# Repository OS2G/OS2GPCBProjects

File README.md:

# OS2GPCBProjects
Repo for the PCB projects

## Resources:

- [Keyboard Project Example](https://www.masterzen.fr/2020/05/03/designing-a-keyboard-part-1/)
- [Part Schematics](https://app.ultralibrarian.com/details/718f6c74-6ffb-11eb-9033-0a34d6323d74/Raspberry-Pi/RP2040)
- [Dr Bauer Kicard Intro Videos](https://youtube.com/@markatlnk5982?feature=shared)
- [RP2040 Spec Sheet](https://datasheets.raspberrypi.com/rp2040/rp2040-datasheet.pdf)
- [Mechanical Keyboard Explained](https://www.daskeyboard.com/blog/parts-of-a-mechanical-keyboard/)
- [Pico Keyboard](https://learn.adafruit.com/diy-pico-mechanical-keyboard-with-fritzing-circuitpython/overview)
- [Quantum Mechanical Keyboard(keyboard controller thing)](https://docs.qmk.fm/#/)

## What Needs Done:

Kickoff The Project: Complete

* Research:
  - How do keyboards talk to a computer: In Progress - Cameron
  - How do we read that a switch has been pressed: In Progress - Cale
  - How do we address the leds to control them:
  - How many gpio/controller ports do we need. AKA, do we need multiple controllers: In Progress - Jacob

* PCB - Numpad:
  - Design Wiring Schematic:
  - Pick Parts:
  - Pick Switches/Keys:
  - Do PCB Connections:
  - Order PCB:
  - Solder:
  - Make Controller (software):
  - Test:
  - Make Walkthrough/Documentation:

* Case Design: 
  - Mounting:
  - Design Case:
  - 3d Print Case:

* PCB -  Keyboard:
  - Design Wiring Schematic:
  - Pick Parts:
  - Pick Switches/Keys:
  - Do PCB Connections:
  - Order PCB:
  - Solder:
  - Make Controller (software):
  - Test:
  - Make Walkthrough/Documentation:

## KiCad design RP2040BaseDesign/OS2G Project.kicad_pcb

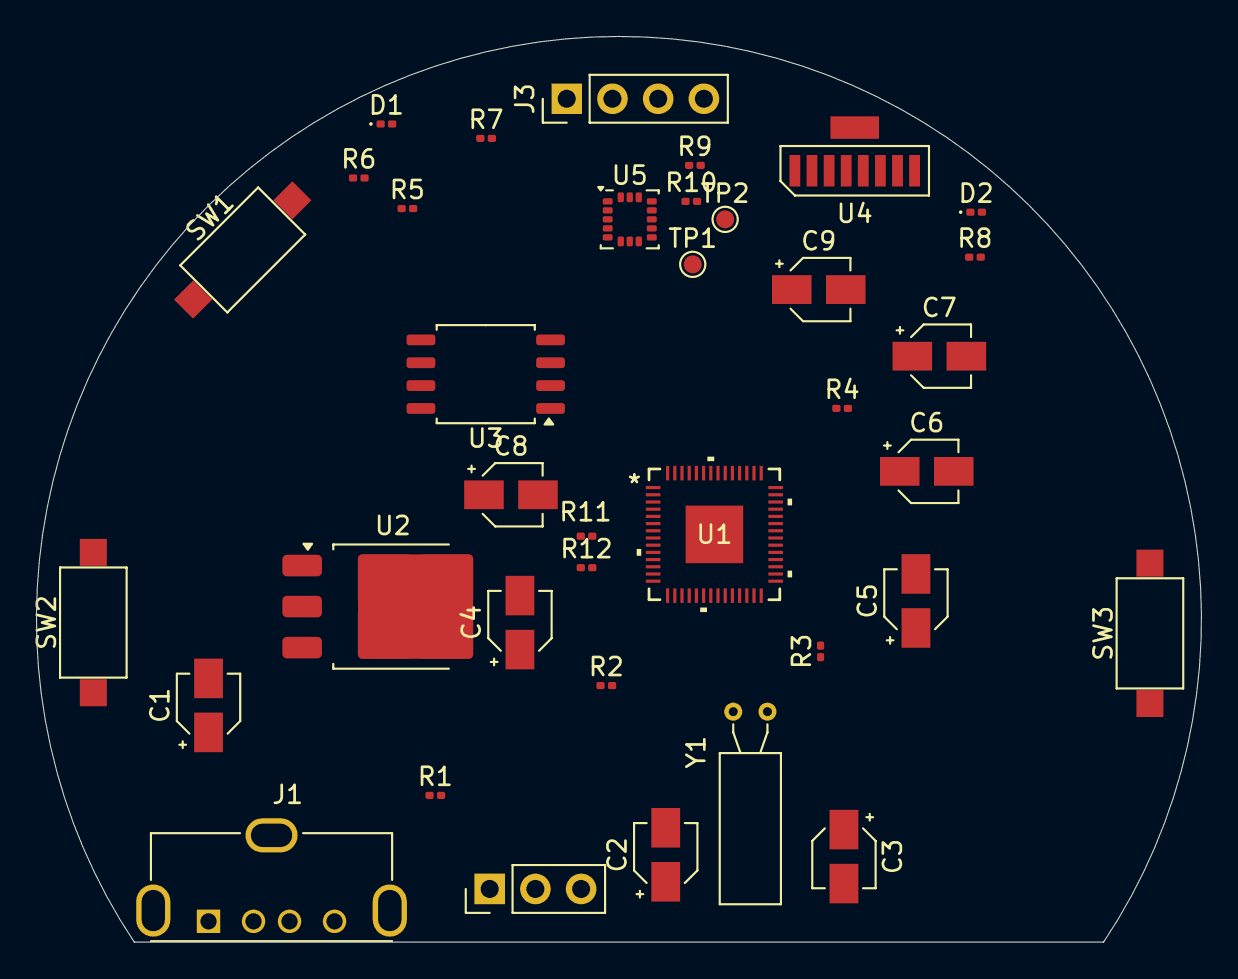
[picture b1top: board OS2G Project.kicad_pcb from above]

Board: 2 copper layers, 64.7 x 50.3 mm, 37 parts (0 on the bottom side), 34 nets, no tracks yet.

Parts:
C1, C2, C8: 100nF; CP_Elec_3x5.3
C3, C4: 15pF; CP_Elec_3x5.3
C5, C6, C7, C9: 10mF; CP_Elec_3x5.3
D1, D2: LED; LED_0201_0603Metric
J1: USB_B_Micro; USB_A_Molex_105057_Vertical
J2: Conn_01x03; PinHeader_1x03_P2.54mm_Vertical
J3: Conn_01x04; PinHeader_1x04_P2.54mm_Vertical
R1, R2: 27; R_0201_0603Metric
R3, R5: 10K; R_0201_0603Metric
R4: 100; R_0201_0603Metric
R6, R7, R8: 1K; R_0201_0603Metric
R9, R10, R11, R12: 4.7k; R_0201_0603Metric
SW1, SW2, SW3: SW_Push; SW_SPST_CK_RS282G05A3
TP1, TP2: TestPoint; TestPoint_Pad_D1.0mm
U1: RP2040; IC57_RP2040
U2: AMS1117CD-3.3; TO-252-3_TabPin2
U3: W25Q32JVSS; SOIC-8_5.23x5.23mm_P1.27mm
U4: HSDL_3201
U5: LIS3DH; LGA-16_3x3mm_P0.5mm_LayoutBorder3x5y
Y1: 12Mhz; Crystal_C38-LF_D3.0mm_L8.0mm_Horizontal

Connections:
+1V1: C5.1, U1.23 (DVDD), U1.45 (VREG_VOUT), U1.50 (DVDD)
+3.3V: C2.1, C6.1, C8.1, C9.1, J3.2, R3.1, R4.2, R5.2, R9.2, R10.2, R11.2, R12.2, U1.1 (IOVDD), U1.10 (IOVDD), U1.22 (IOVDD), U1.33 (IOVDD), U1.42 (IOVDD), U1.44 (VREG_VIN), U1.48 (USB_VDD), U1.49 (IOVDD), U2.2 (VO), U3.8 (VCC), U4.3 (VCC), U4.8 (VLED), U5.1 (VDD_IO), U5.8 (CS), U5.14 (VDD)
+5V: C1.1, J1.1 (VBUS), U2.3 (VI)
Button1: R11.1, SW2.1, U1.9 (GPIO7)
Button2: R12.1, SW3.1, U1.11 (GPIO8)
GND: C1.2, C2.2, C3.2, C4.2, C5.2, C6.2, C7.2, C8.2, C9.2, D1.1 (K), D2.1 (K), J1.5 (GND), J2.2, J3.1, SW1.1, SW2.2, SW3.2, U1.19 (TESTEN), U1.57 (GND), U2.1 (GND), U3.4 (GND), U4.1 (GND), U4.4 (AGND), U4.9 (SHIELD), U5.5 (GND), U5.10 (GND), U5.12 (GND)
IO0: U1.53 (QSPI_SD0), U3.5 (DI(IO0))
IO1: U1.55 (QSPI_SD1), U3.2 (DO(IO1))
IO2: U1.54 (QSPI_SD2), U3.3 (IO2)
IO3: U1.51 (QSPI_SD3), U3.7 (IO3)
IRDA_RX: U1.6 (GPIO4), U4.6 (RXD)
IRDA_SD: U1.8 (GPIO6), U4.5 (SD)
IRDA_TX: U1.7 (GPIO5), U4.7 (TXD)
LED0: R7.2, U1.2 (GPIO0)
LED1: R8.2, U1.3 (GPIO1)
MCLK: U1.52 (QSPI_SCLK), U3.6 (CLK)
MCS: R5.1, R6.2, U1.56 (QSPI_SS_N), U3.1 (~CS)
unnamed: D1.2 (A), R7.1
unnamed: D2.2 (A), R8.1
unnamed: J1.3 (D+), R1.1
unnamed: J1.2 (D-), R2.1
unnamed: R6.1, SW1.2
unnamed: C7.1, R4.1, U1.43 (ADC_AVDD)
unnamed: R3.2, U1.26 (RUN)
unnamed: TP1.1, U5.11 (INT1)
unnamed: TP2.1, U5.9 (INT2)
SCL: J3.3, R10.1, U1.5 (GPIO3), U5.4 (SCL/SPC)
SDA: J3.4, R9.1, U1.4 (GPIO2), U5.6 (SDA/SDI/SDO)
SWCLK: J2.1, U1.24 (SWCLK)
SWDIO: J2.3, U1.25 (SWDIO)
USB_DM: R2.2, U1.46 (USB_DM)
USB_DP: R1.2, U1.47 (USB_DP)
X0: C3.1, U1.20 (XIN), Y1.1
X1: C4.1, U1.21 (XOUT)

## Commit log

2024-03-02 initial push for the PCB project, contains rp2040 base design
2024-03-05 Update README.md
    Added some resources that may be useful
2024-03-05 Update README.md
    Added mechanical keyboard part explanation
2024-03-09 made better formatting
2024-03-09 embedded links
2024-03-09 made keyboard directory
